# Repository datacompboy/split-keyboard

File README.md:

# My very own split keyboard.

Read tutorial on how to build it [in english](how-to-make/building.md) or [in russian](how-to-make/building-ru.md).

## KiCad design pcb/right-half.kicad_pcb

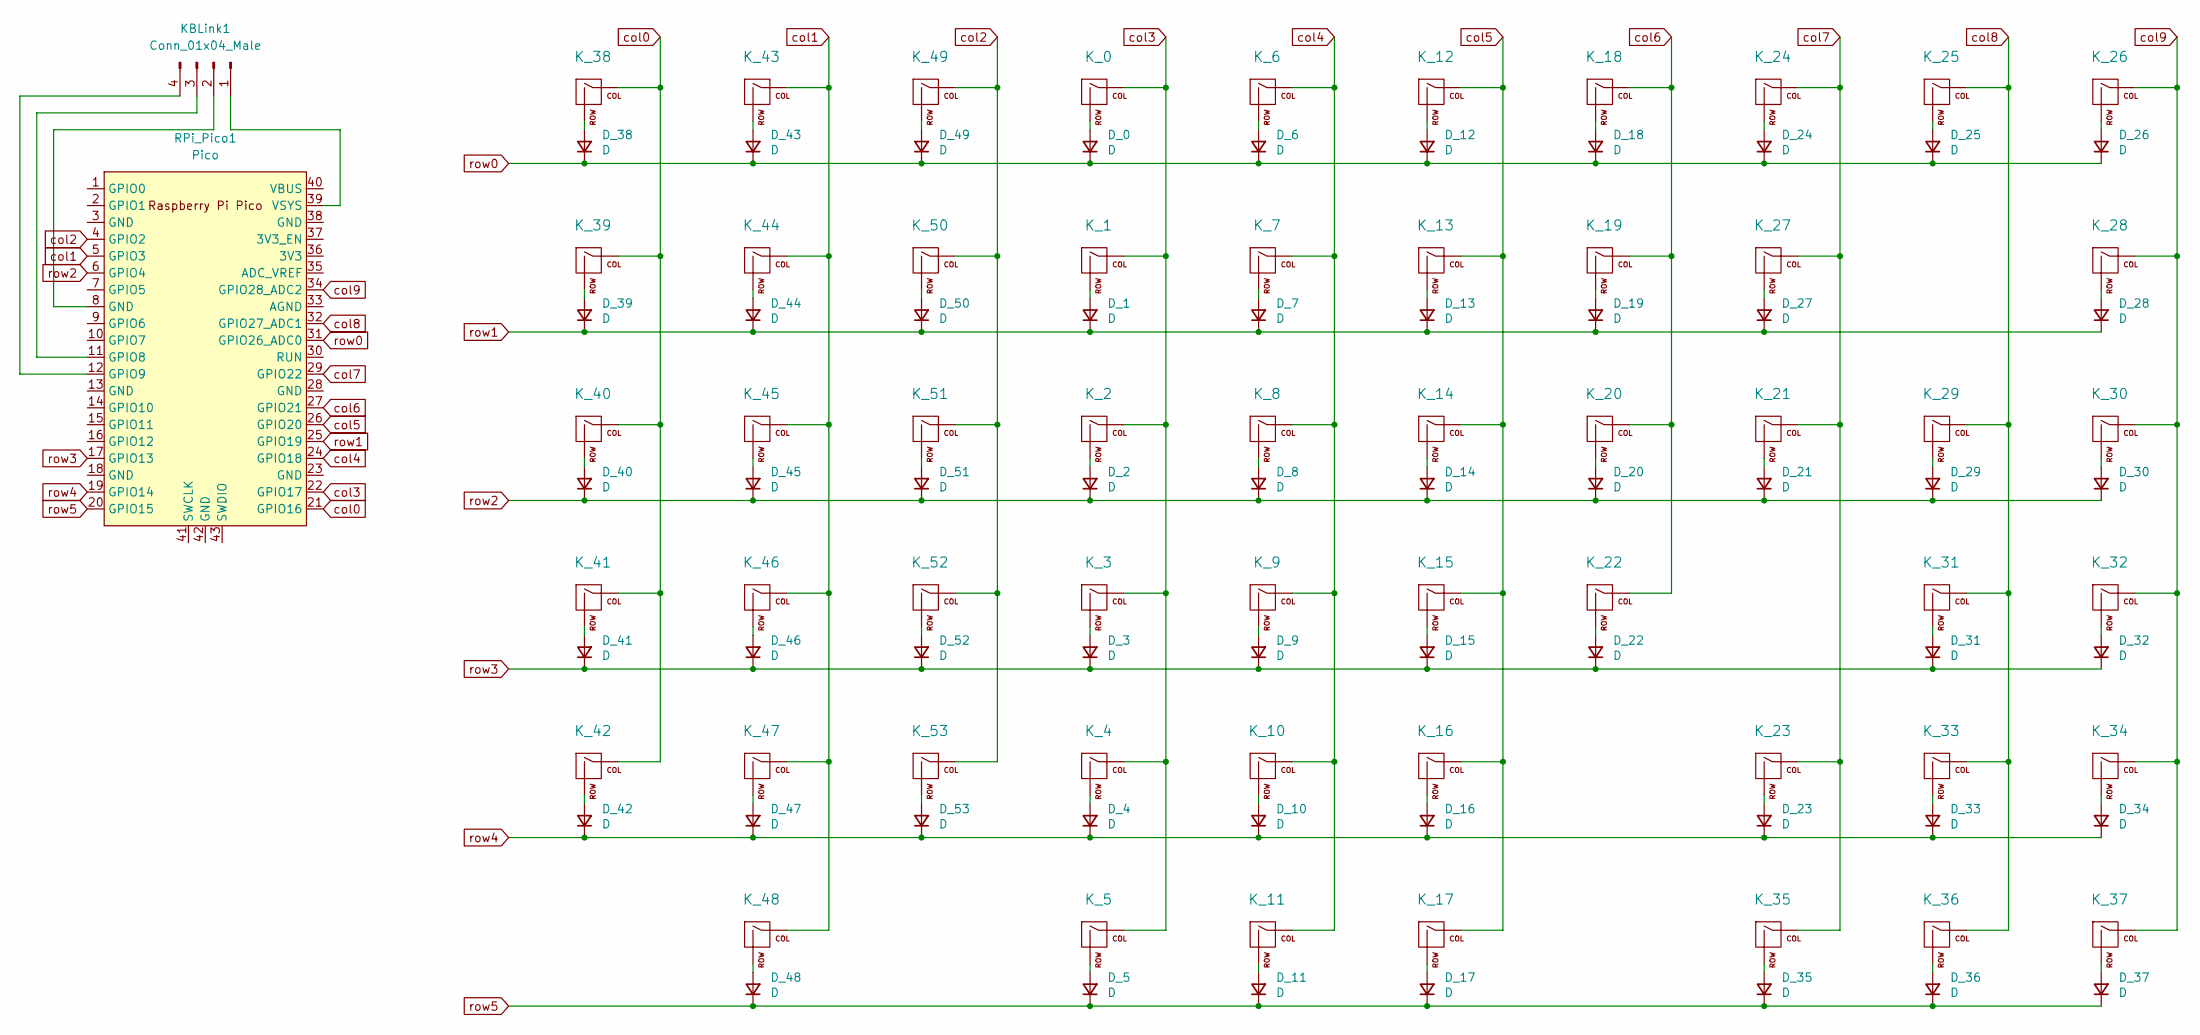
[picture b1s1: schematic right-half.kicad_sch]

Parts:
D_0, D_1, D_2, D_3, D_4, D_5, D_6, D_7, D_8, D_9, D_10, D_11, D_12, D_13, D_14, D_15, D_16, D_17, D_18, D_19, D_20, D_21, D_22, D_23, D_24, D_25, D_26, D_27, D_28, D_29, D_30, D_31, D_32, D_33, D_34, D_35, D_36, D_37, D_38, D_39, D_40, D_41, D_42, D_43, D_44, D_45, D_46, D_47, D_48, D_49, D_50, D_51, D_52, D_53: D; D_SOD-123
KBLink1: Conn_01x04_Male; JST_SH_SM04B-SRSS-TB_1x04-1MP_P1.00mm_Horizontal
K_0, K_1, K_2, K_3, K_4, K_6, K_7, K_8, K_9, K_10, K_11, K_12, K_13, K_14, K_15, K_16, K_18, K_19, K_20, K_21, K_22, K_24, K_25, K_26, K_28, K_30, K_32, K_33, K_34, K_35, K_36, K_37, K_38, K_39, K_40, K_41, K_42, K_43, K_44, K_45, K_46, K_47, K_49, K_50, K_51, K_52, K_53: KEYSW; MX-1U-NoLED
K_5, K_29: KEYSW; MX-1.5U-NoLED
K_17: KEYSW; MX-1.25U-NoLED
K_23: KEYSW; MX-1.75U-NoLED
K_27: KEYSW; MX-2.25U-NoLED
K_31: KEYSW; MX-2U-NoLED
K_48: KEYSW; MX-2.75U-NoLED
RPi_Pico1: Pico; RPi_Pico_SMD_TH

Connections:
unnamed: D_0.2 (A), K_0.2 (ROW)
unnamed: D_1.2 (A), K_1.2 (ROW)
unnamed: D_2.2 (A), K_2.2 (ROW)
unnamed: D_3.2 (A), K_3.2 (ROW)
unnamed: D_4.2 (A), K_4.2 (ROW)
unnamed: D_5.2 (A), K_5.2 (ROW)
unnamed: D_6.2 (A), K_6.2 (ROW)
unnamed: D_7.2 (A), K_7.2 (ROW)
unnamed: D_8.2 (A), K_8.2 (ROW)
unnamed: D_9.2 (A), K_9.2 (ROW)
unnamed: D_10.2 (A), K_10.2 (ROW)
unnamed: D_11.2 (A), K_11.2 (ROW)
unnamed: D_12.2 (A), K_12.2 (ROW)
unnamed: D_13.2 (A), K_13.2 (ROW)
unnamed: D_14.2 (A), K_14.2 (ROW)
unnamed: D_15.2 (A), K_15.2 (ROW)
unnamed: D_16.2 (A), K_16.2 (ROW)
unnamed: D_17.2 (A), K_17.2 (ROW)
unnamed: D_18.2 (A), K_18.2 (ROW)
unnamed: D_19.2 (A), K_19.2 (ROW)
unnamed: D_20.2 (A), K_20.2 (ROW)
unnamed: D_21.2 (A), K_21.2 (ROW)
unnamed: D_22.2 (A), K_22.2 (ROW)
unnamed: D_23.2 (A), K_23.2 (ROW)
unnamed: D_24.2 (A), K_24.2 (ROW)
unnamed: D_25.2 (A), K_25.2 (ROW)
unnamed: D_26.2 (A), K_26.2 (ROW)
unnamed: D_27.2 (A), K_27.2 (ROW)
unnamed: D_28.2 (A), K_28.2 (ROW)
unnamed: D_29.2 (A), K_29.2 (ROW)
unnamed: D_30.2 (A), K_30.2 (ROW)
unnamed: D_31.2 (A), K_31.2 (ROW)
unnamed: D_32.2 (A), K_32.2 (ROW)
unnamed: D_33.2 (A), K_33.2 (ROW)
unnamed: D_34.2 (A), K_34.2 (ROW)
unnamed: D_35.2 (A), K_35.2 (ROW)
unnamed: D_36.2 (A), K_36.2 (ROW)
unnamed: D_37.2 (A), K_37.2 (ROW)
unnamed: D_38.2 (A), K_38.2 (ROW)
unnamed: D_39.2 (A), K_39.2 (ROW)
unnamed: D_40.2 (A), K_40.2 (ROW)
unnamed: D_41.2 (A), K_41.2 (ROW)
unnamed: D_42.2 (A), K_42.2 (ROW)
unnamed: D_43.2 (A), K_43.2 (ROW)
unnamed: D_44.2 (A), K_44.2 (ROW)
unnamed: D_45.2 (A), K_45.2 (ROW)
unnamed: D_46.2 (A), K_46.2 (ROW)
unnamed: D_47.2 (A), K_47.2 (ROW)
unnamed: D_48.2 (A), K_48.2 (ROW)
unnamed: D_49.2 (A), K_49.2 (ROW)
unnamed: D_50.2 (A), K_50.2 (ROW)
unnamed: D_51.2 (A), K_51.2 (ROW)
unnamed: D_52.2 (A), K_52.2 (ROW)
unnamed: D_53.2 (A), K_53.2 (ROW)
unnamed: KBLink1.1, RPi_Pico1.39 (VSYS)
unnamed: KBLink1.2, RPi_Pico1.8 (GND)
unnamed: KBLink1.3, RPi_Pico1.11 (GPIO8)
unnamed: KBLink1.4, RPi_Pico1.12 (GPIO9)
col0: K_38.1 (COL), K_39.1 (COL), K_40.1 (COL), K_41.1 (COL), K_42.1 (COL), RPi_Pico1.21 (GPIO16)
col1: K_43.1 (COL), K_44.1 (COL), K_45.1 (COL), K_46.1 (COL), K_47.1 (COL), K_48.1 (COL), RPi_Pico1.5 (GPIO3)
col2: K_49.1 (COL), K_50.1 (COL), K_51.1 (COL), K_52.1 (COL), K_53.1 (COL), RPi_Pico1.4 (GPIO2)
col3: K_0.1 (COL), K_1.1 (COL), K_2.1 (COL), K_3.1 (COL), K_4.1 (COL), K_5.1 (COL), RPi_Pico1.22 (GPIO17)
col4: K_6.1 (COL), K_7.1 (COL), K_8.1 (COL), K_9.1 (COL), K_10.1 (COL), K_11.1 (COL), RPi_Pico1.24 (GPIO18)
col5: K_12.1 (COL), K_13.1 (COL), K_14.1 (COL), K_15.1 (COL), K_16.1 (COL), K_17.1 (COL), RPi_Pico1.26 (GPIO20)
col6: K_18.1 (COL), K_19.1 (COL), K_20.1 (COL), K_22.1 (COL), RPi_Pico1.27 (GPIO21)
col7: K_21.1 (COL), K_23.1 (COL), K_24.1 (COL), K_27.1 (COL), K_35.1 (COL), RPi_Pico1.29 (GPIO22)
col8: K_25.1 (COL), K_29.1 (COL), K_31.1 (COL), K_33.1 (COL), K_36.1 (COL), RPi_Pico1.32 (GPIO27_ADC1)
col9: K_26.1 (COL), K_28.1 (COL), K_30.1 (COL), K_32.1 (COL), K_34.1 (COL), K_37.1 (COL), RPi_Pico1.34 (GPIO28_ADC2)
row0: D_0.1 (K), D_6.1 (K), D_12.1 (K), D_18.1 (K), D_24.1 (K), D_25.1 (K), D_26.1 (K), D_38.1 (K), D_43.1 (K), D_49.1 (K), RPi_Pico1.31 (GPIO26_ADC0)
row1: D_1.1 (K), D_7.1 (K), D_13.1 (K), D_19.1 (K), D_27.1 (K), D_28.1 (K), D_39.1 (K), D_44.1 (K), D_50.1 (K), RPi_Pico1.25 (GPIO19)
row2: D_2.1 (K), D_8.1 (K), D_14.1 (K), D_20.1 (K), D_21.1 (K), D_29.1 (K), D_30.1 (K), D_40.1 (K), D_45.1 (K), D_51.1 (K), RPi_Pico1.6 (GPIO4)
row3: D_3.1 (K), D_9.1 (K), D_15.1 (K), D_22.1 (K), D_31.1 (K), D_32.1 (K), D_41.1 (K), D_46.1 (K), D_52.1 (K), RPi_Pico1.17 (GPIO13)
row4: D_4.1 (K), D_10.1 (K), D_16.1 (K), D_23.1 (K), D_33.1 (K), D_34.1 (K), D_42.1 (K), D_47.1 (K), D_53.1 (K), RPi_Pico1.19 (GPIO14)
row5: D_5.1 (K), D_11.1 (K), D_17.1 (K), D_35.1 (K), D_36.1 (K), D_37.1 (K), D_48.1 (K), RPi_Pico1.20 (GPIO15)

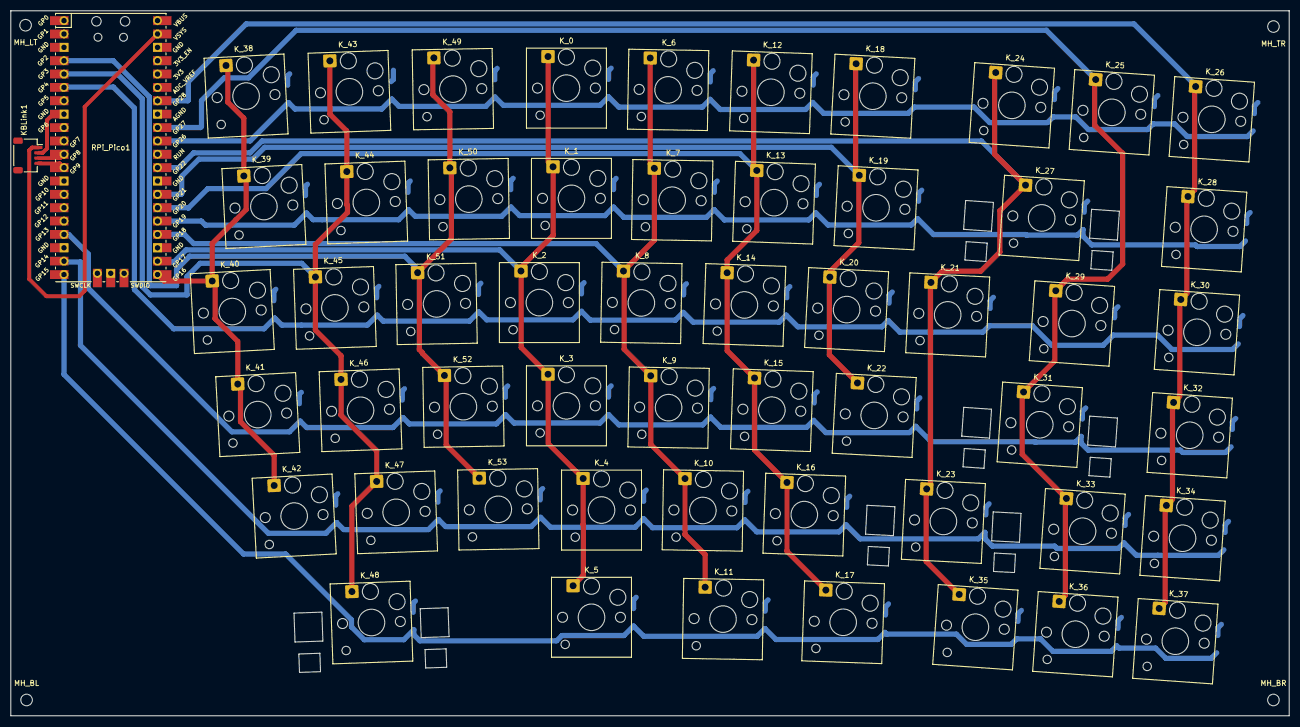
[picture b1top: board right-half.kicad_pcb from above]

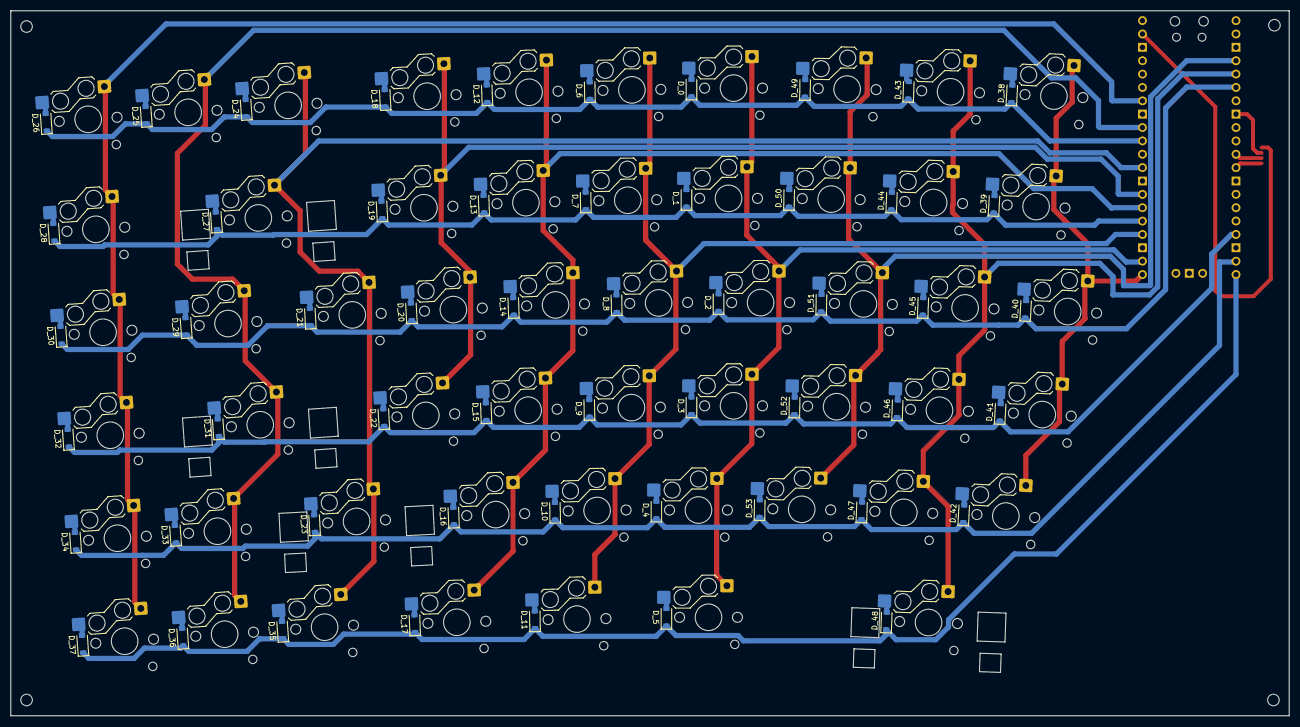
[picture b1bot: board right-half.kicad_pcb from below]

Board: 2 copper layers, 243.0 x 134.0 mm, 118 parts (54 on the bottom side), 74 nets.

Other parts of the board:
MH_BL: MountingHole_2.2mm_M2
MH_BR: MountingHole_2.2mm_M2
MH_LT: MountingHole_2.2mm_M2
MH_TR: MountingHole_2.2mm_M2
ST_23, ST_27, ST_31, ST_48: Choc; Stab-PG1350-2u.kicad_mod

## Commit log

2022-06-06 Seed README with pointer to the articles series.
2022-06-06 Keyboard Layout for halves including generated files
2022-06-06 PCB for the keyboard including packages for ordering.
2022-06-06 Fix MD format
2022-06-10 Upload first two chapters
2022-06-12 Upload QMK keyboard firmware files
2022-06-12 Publish chapter 3
